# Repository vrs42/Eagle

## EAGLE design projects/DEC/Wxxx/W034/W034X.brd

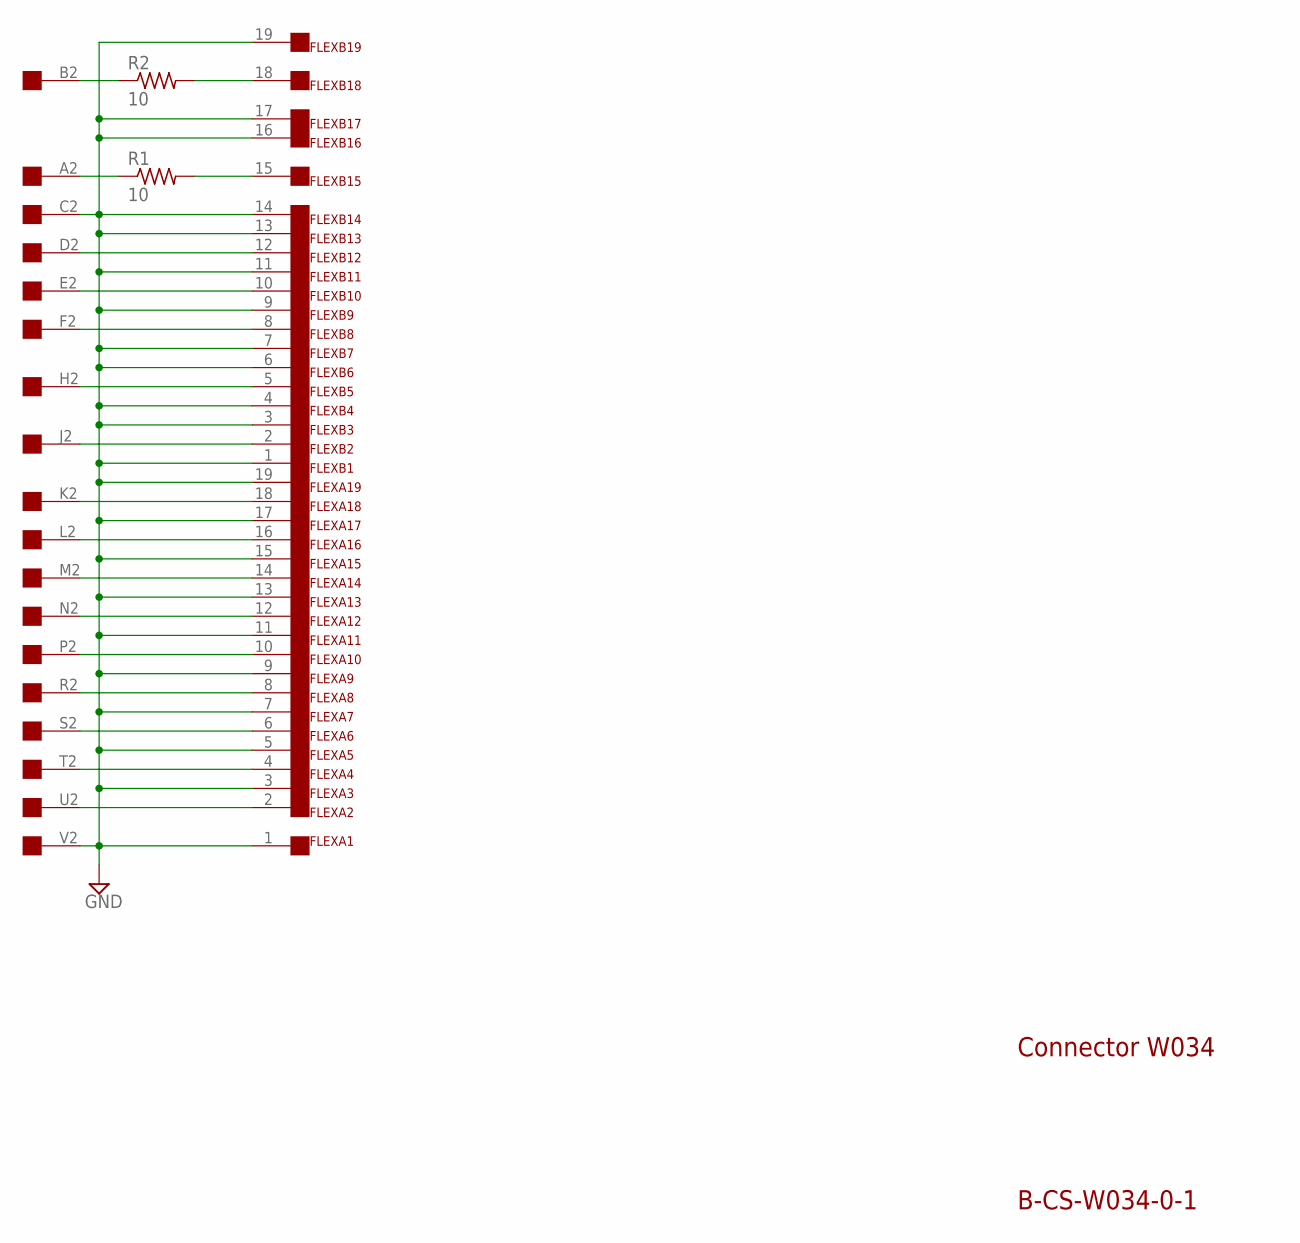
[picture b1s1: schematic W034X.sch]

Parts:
FLEXA: FLEX19
FLEXB: FLEX19
R1, R2: 10; 0207/10
U$2: EDGE-1; EDGE-CON1

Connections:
GND: FLEXA.1, FLEXA.3, FLEXA.5, FLEXA.7, FLEXA.9, FLEXA.11, FLEXA.13, FLEXA.15, FLEXA.17, FLEXA.19, FLEXB.1, FLEXB.3, FLEXB.4, FLEXB.6, FLEXB.7, FLEXB.9, FLEXB.11, FLEXB.13, FLEXB.14, FLEXB.16, FLEXB.17, FLEXB.19, U$2.C2, U$2.V2
unnamed: FLEXB.10, U$2.E2
unnamed: FLEXB.5, U$2.H2
unnamed: FLEXA.18, U$2.K2
unnamed: FLEXA.14, U$2.M2
unnamed: FLEXA.10, U$2.P2
unnamed: FLEXA.6, U$2.S2
unnamed: FLEXA.4, U$2.T2
unnamed: FLEXA.8, U$2.R2
unnamed: FLEXB.12, U$2.D2
unnamed: R2.1, U$2.B2
unnamed: R1.1, U$2.A2
unnamed: FLEXB.18, R2.2
unnamed: FLEXB.15, R1.2
unnamed: FLEXA.2, U$2.U2
unnamed: FLEXB.8, U$2.F2
unnamed: FLEXB.2, U$2.J2
unnamed: FLEXA.16, U$2.L2
unnamed: FLEXA.12, U$2.N2

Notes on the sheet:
Connector W034
B-CS-W034-0-1

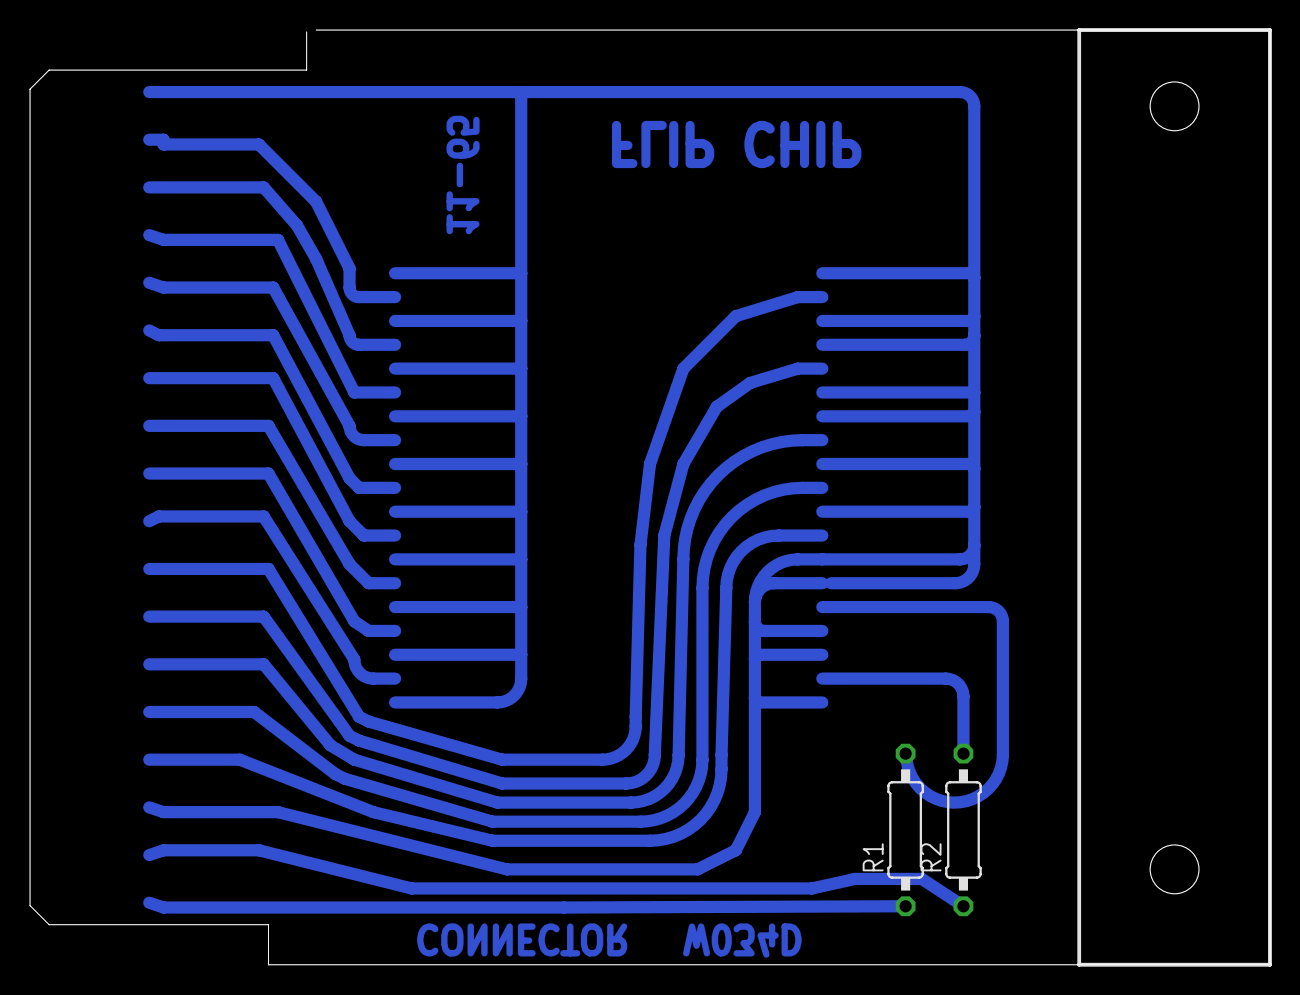
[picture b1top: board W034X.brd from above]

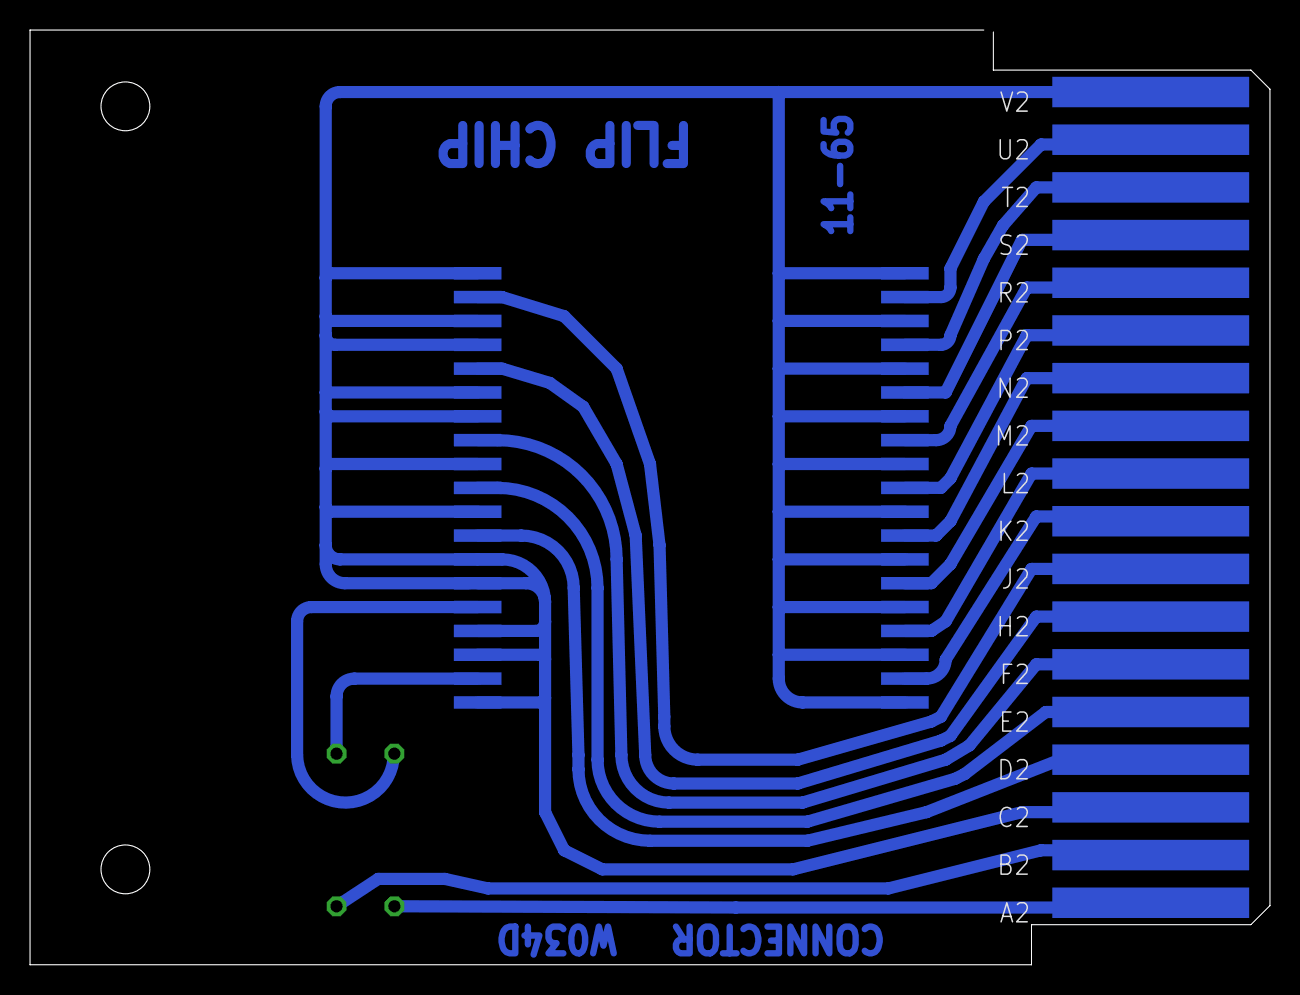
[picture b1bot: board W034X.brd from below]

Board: 2 copper layers, 82.5 x 62.2 mm, 5 parts (2 on the bottom side), 19 nets.

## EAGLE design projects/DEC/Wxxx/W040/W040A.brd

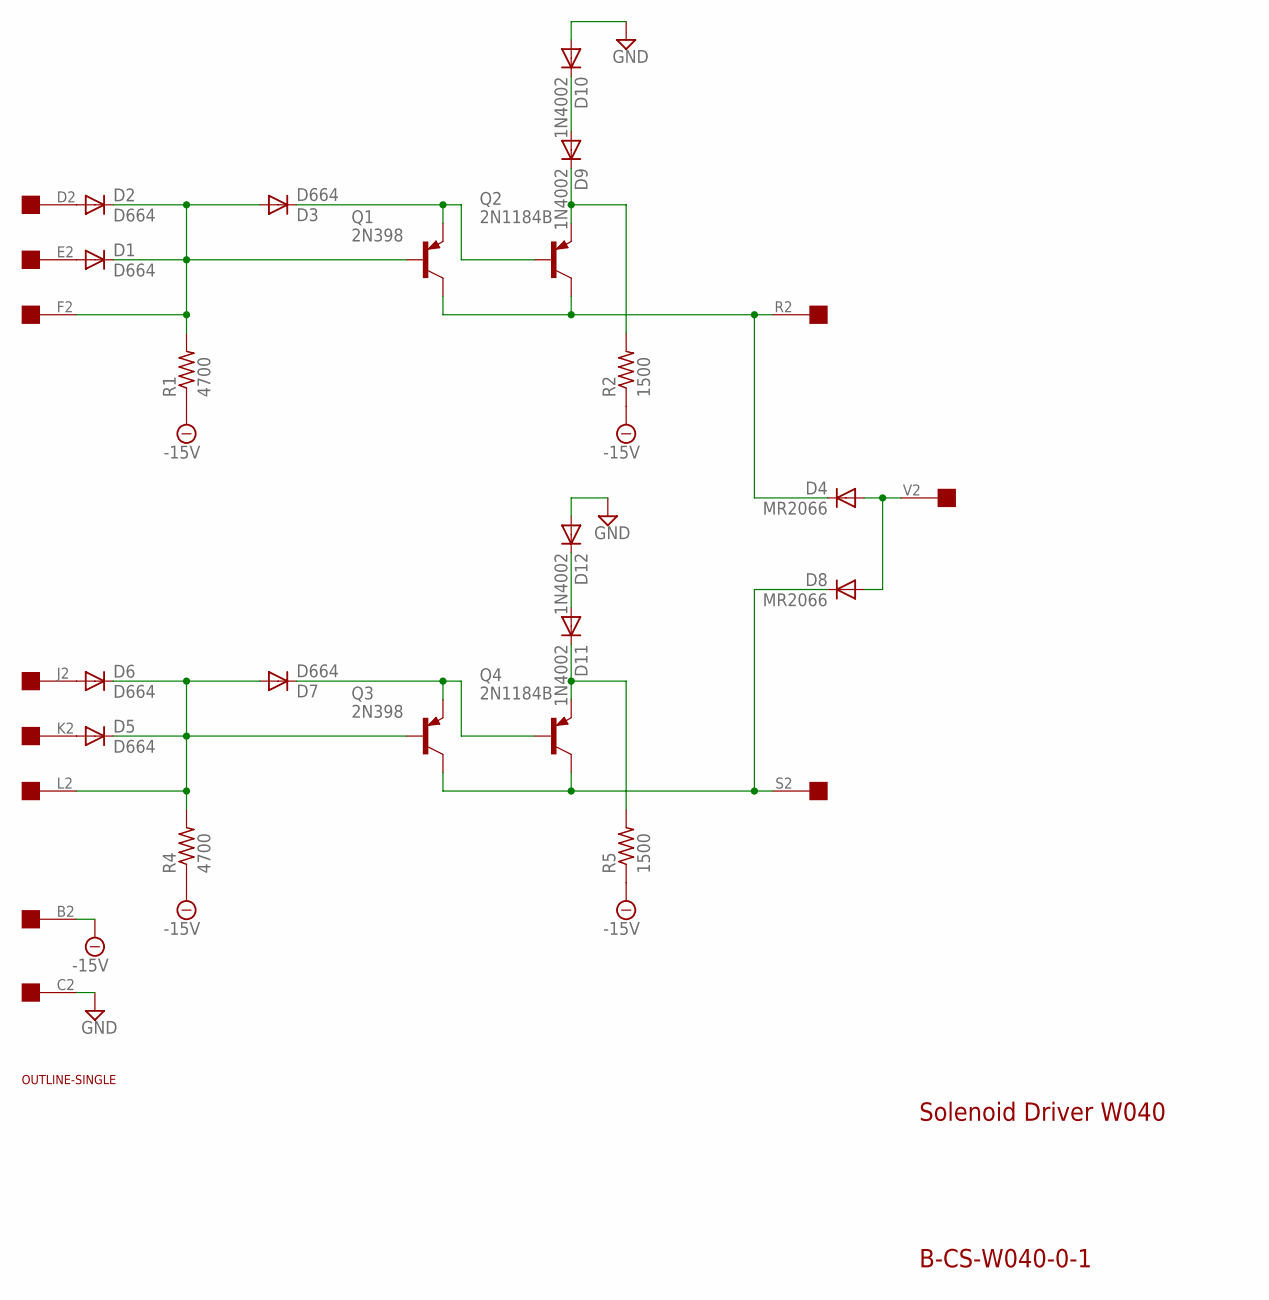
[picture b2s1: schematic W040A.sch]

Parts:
D1, D2, D3, D5, D6, D7: D664; DO35-10
D4, D8: MR2066; DO41-10
D9, D10, D11, D12: 1N4002; DO41-10
Q1, Q3: 2N398; TO39
Q2, Q4: 2N1184B; TO5
R1, R4: 4700; 0207/10
R2, R5: 1500; 0207/10
U$1: OUTLINE-SINGLE; SINGLE
U$2: EDGE-1; EDGE-CON1

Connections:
-15V: R1.1, R2.1, R4.1, R5.1, U$2.B2
GND: D10.A, D12.A, U$2.C2
unnamed: D1.A, U$2.E2
unnamed: D2.A, U$2.D2
unnamed: D1.C, D2.C, D3.A, Q1.2 (B), R1.2, U$2.F2
unnamed: D3.C, Q1.1 (E), Q2.2 (B)
unnamed: D9.A, D10.C
unnamed: D4.A, D8.A, U$2.V2
unnamed: D4.C, Q1.3 (C), Q2.3 (C), U$2.R2
unnamed: D5.A, U$2.K2
unnamed: D6.A, U$2.J2
unnamed: D5.C, D6.C, D7.A, Q3.2 (B), R4.2, U$2.L2
unnamed: D7.C, Q3.1 (E), Q4.2 (B)
unnamed: D9.C, Q2.1 (E), R2.2
unnamed: D8.C, Q3.3 (C), Q4.3 (C), U$2.S2
unnamed: D11.C, Q4.1 (E), R5.2
unnamed: D11.A, D12.C

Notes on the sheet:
Solenoid Driver W040
B-CS-W040-0-1

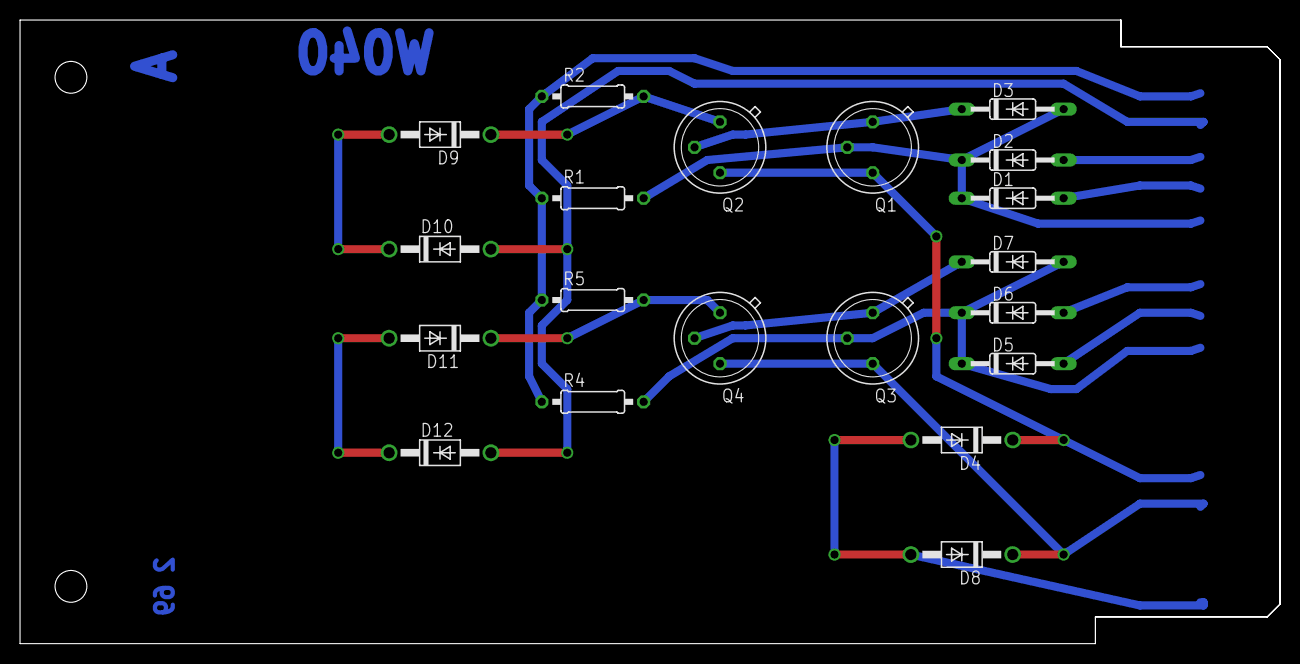
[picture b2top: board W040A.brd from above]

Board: 2 copper layers, 125.7 x 62.2 mm, 22 parts (0 on the bottom side), 17 nets.

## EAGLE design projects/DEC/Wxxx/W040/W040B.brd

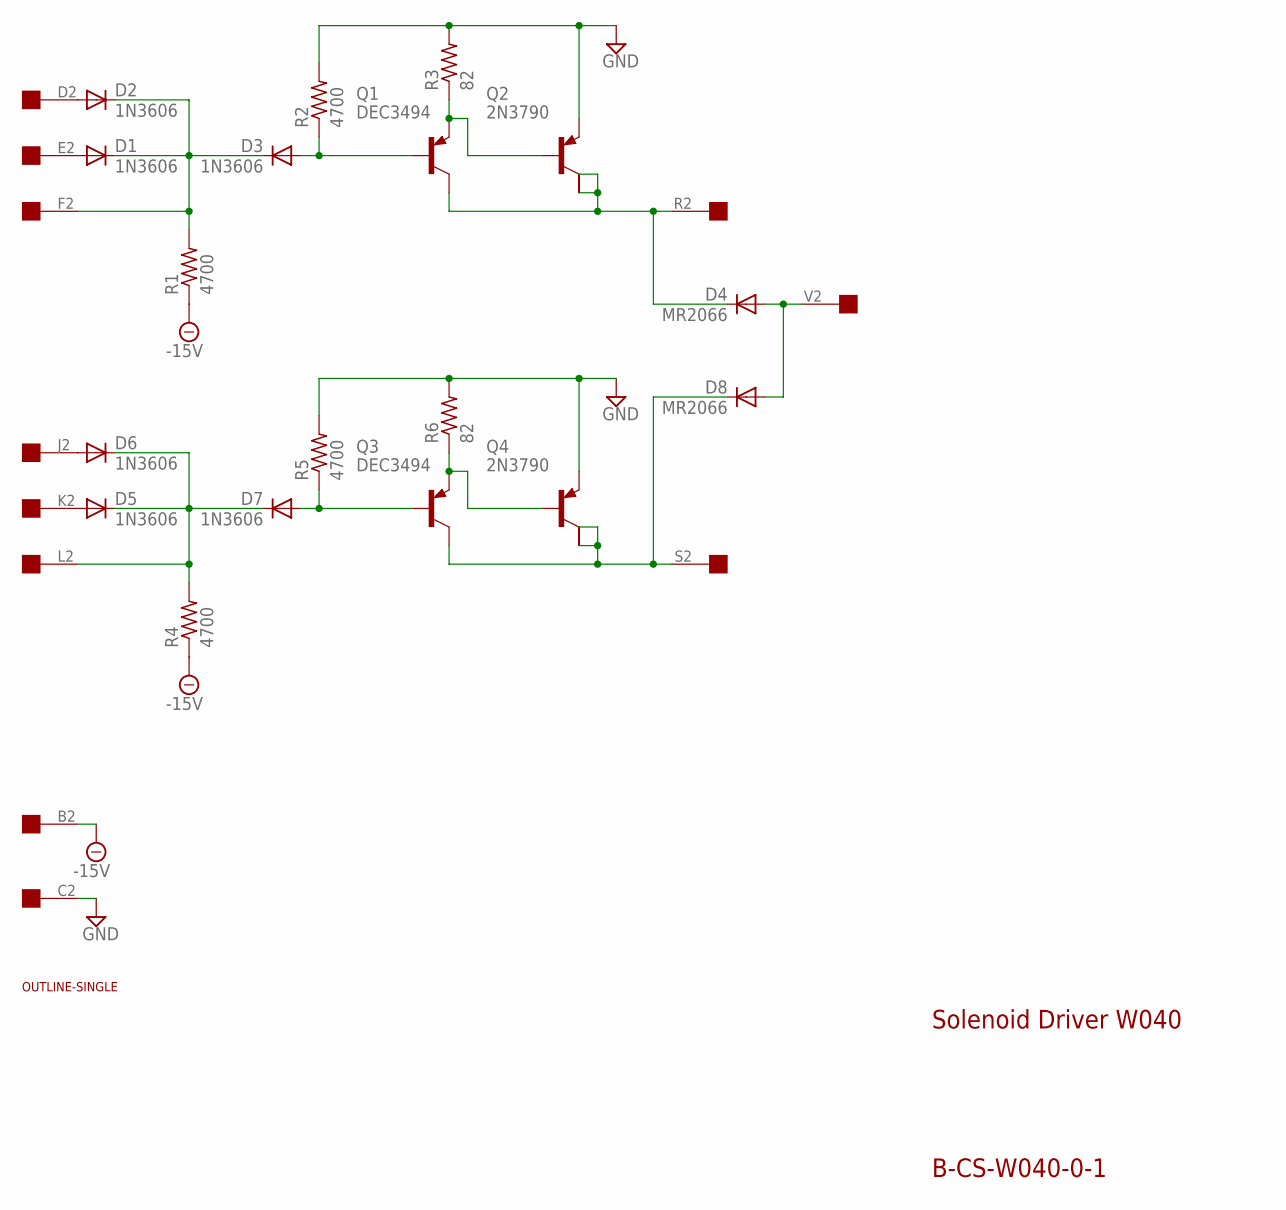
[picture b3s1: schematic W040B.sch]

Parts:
D1, D2, D3, D5, D6, D7: 1N3606; DO35-10
D4, D8: MR2066; DO41-10
Q1, Q3: DEC3494; TO39
Q2, Q4: 2N3790; TO3
R1, R2, R4, R5: 4700; 0207/10
R3, R6: 82; 0207/10
U$1: OUTLINE-SINGLE; SINGLE
U$2: EDGE-1; EDGE-CON1

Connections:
-15V: R1.1, R4.1, U$2.B2
GND: Q2.E, Q4.E, R2.2, R3.2, R5.2, R6.2, U$2.C2
unnamed: D1.A, U$2.E2
unnamed: D2.A, U$2.D2
unnamed: D1.C, D2.C, D3.C, R1.2, U$2.F2
unnamed: D3.A, Q1.2 (B), R2.1
unnamed: Q1.1 (E), Q2.B, R3.1
unnamed: D4.A, D8.A, U$2.V2
unnamed: D4.C, Q1.3 (C), Q2.C, Q2.C/, U$2.R2
unnamed: D5.A, U$2.K2
unnamed: D6.A, U$2.J2
unnamed: D5.C, D6.C, D7.C, R4.2, U$2.L2
unnamed: D7.A, Q3.2 (B), R5.1
unnamed: Q3.1 (E), Q4.B, R6.1
unnamed: D8.C, Q3.3 (C), Q4.C, Q4.C/, U$2.S2

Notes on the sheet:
Solenoid Driver W040
B-CS-W040-0-1

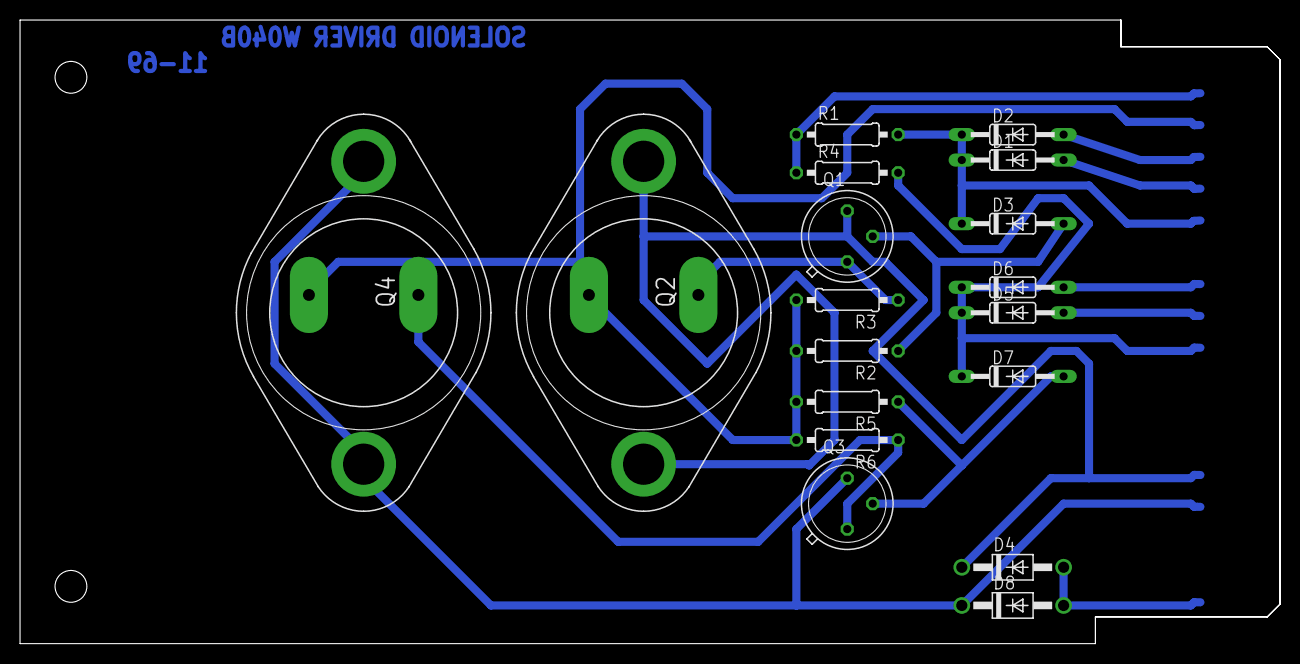
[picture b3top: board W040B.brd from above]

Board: 2 copper layers, 125.7 x 62.2 mm, 20 parts (0 on the bottom side), 15 nets.

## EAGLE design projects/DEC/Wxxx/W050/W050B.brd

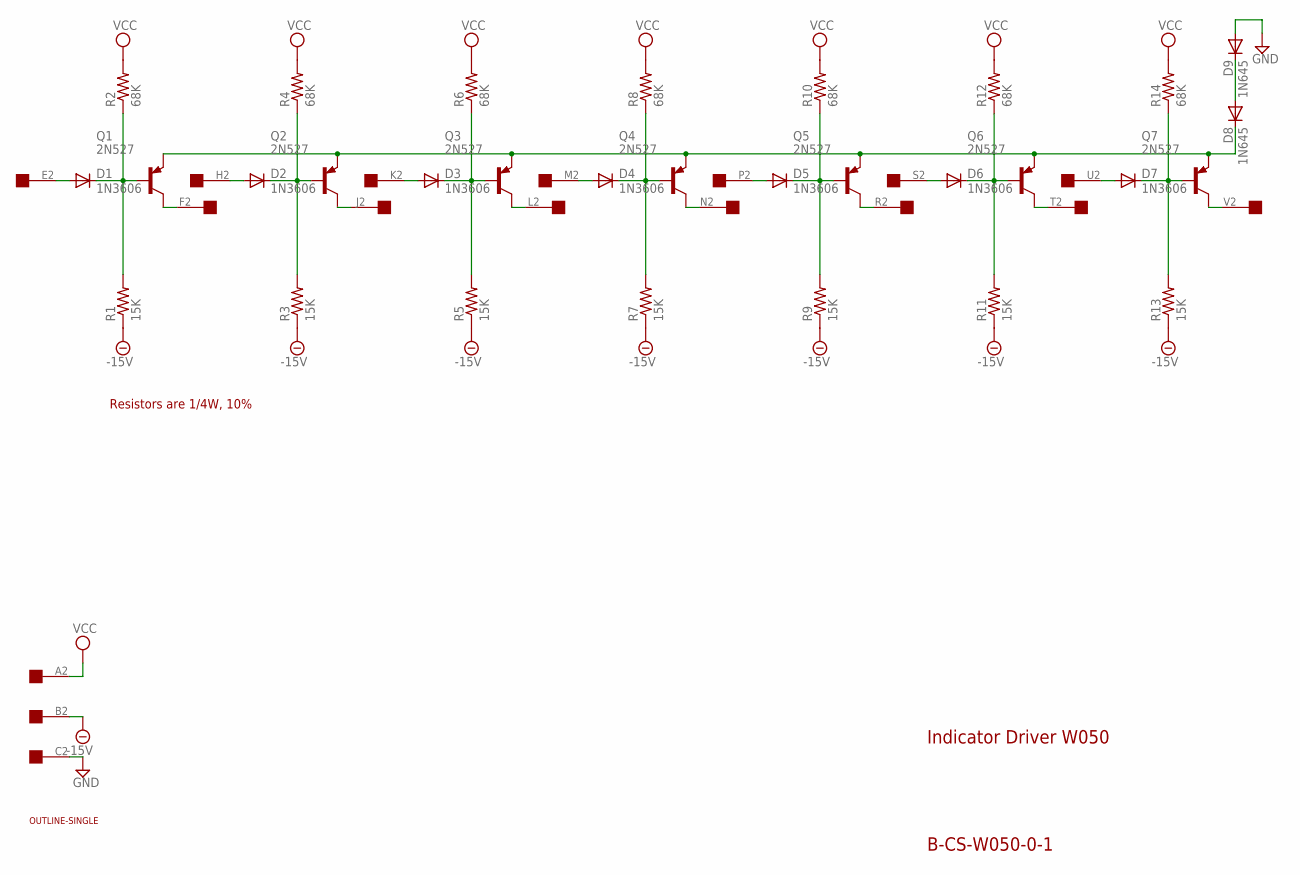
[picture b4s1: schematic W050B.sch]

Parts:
D1, D2, D3, D4, D5, D6, D7: 1N3606; DO35-10
D8, D9: 1N645; DO35-10
EDGE: EDGE-1; EDGE-CON1
Q1, Q2, Q3, Q4, Q5, Q6, Q7: 2N527; TO39
R1, R3, R5, R7, R9, R11, R13: 15K; 0207/10
R2, R4, R6, R8, R10, R12, R14: 68K; 0207/10
U$1: OUTLINE-SINGLE; SINGLE

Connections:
-15V: EDGE.B2, R1.1, R3.1, R5.1, R7.1, R9.1, R11.1, R13.1
GND: D9.A, EDGE.C2
unnamed: D1.C, Q1.2 (B), R1.2, R2.1
unnamed: EDGE.F2, Q1.3 (C)
unnamed: D1.A, EDGE.E2
unnamed: D2.C, Q2.2 (B), R3.2, R4.1
unnamed: EDGE.J2, Q2.3 (C)
unnamed: D6.A, EDGE.S2
unnamed: D4.C, Q4.2 (B), R7.2, R8.1
unnamed: EDGE.N2, Q4.3 (C)
unnamed: D7.A, EDGE.U2
unnamed: D3.C, Q3.2 (B), R5.2, R6.1
unnamed: EDGE.L2, Q3.3 (C)
unnamed: D5.A, EDGE.P2
unnamed: D5.C, Q5.2 (B), R9.2, R10.1
unnamed: EDGE.R2, Q5.3 (C)
unnamed: D4.A, EDGE.M2
unnamed: D6.C, Q6.2 (B), R11.2, R12.1
unnamed: EDGE.T2, Q6.3 (C)
unnamed: D3.A, EDGE.K2
unnamed: D7.C, Q7.2 (B), R13.2, R14.1
unnamed: EDGE.V2, Q7.3 (C)
unnamed: D2.A, EDGE.H2
unnamed: D8.C, Q1.1 (E), Q2.1 (E), Q3.1 (E), Q4.1 (E), Q5.1 (E), Q6.1 (E), Q7.1 (E)
unnamed: D8.A, D9.C
VCC: EDGE.A2, R2.2, R4.2, R6.2, R8.2, R10.2, R12.2, R14.2

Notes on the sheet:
Indicator Driver W050
Resistors are 1/4W, 10%
B-CS-W050-0-1

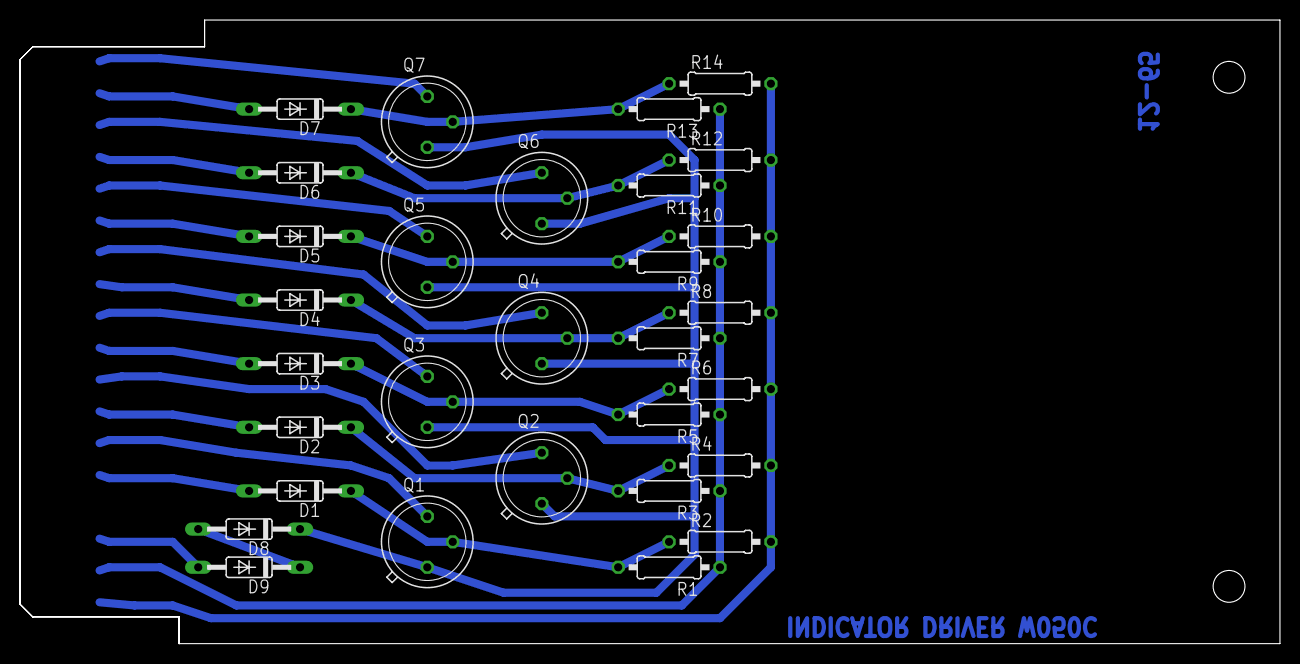
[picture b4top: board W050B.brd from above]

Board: 2 copper layers, 125.7 x 62.2 mm, 32 parts (0 on the bottom side), 26 nets.

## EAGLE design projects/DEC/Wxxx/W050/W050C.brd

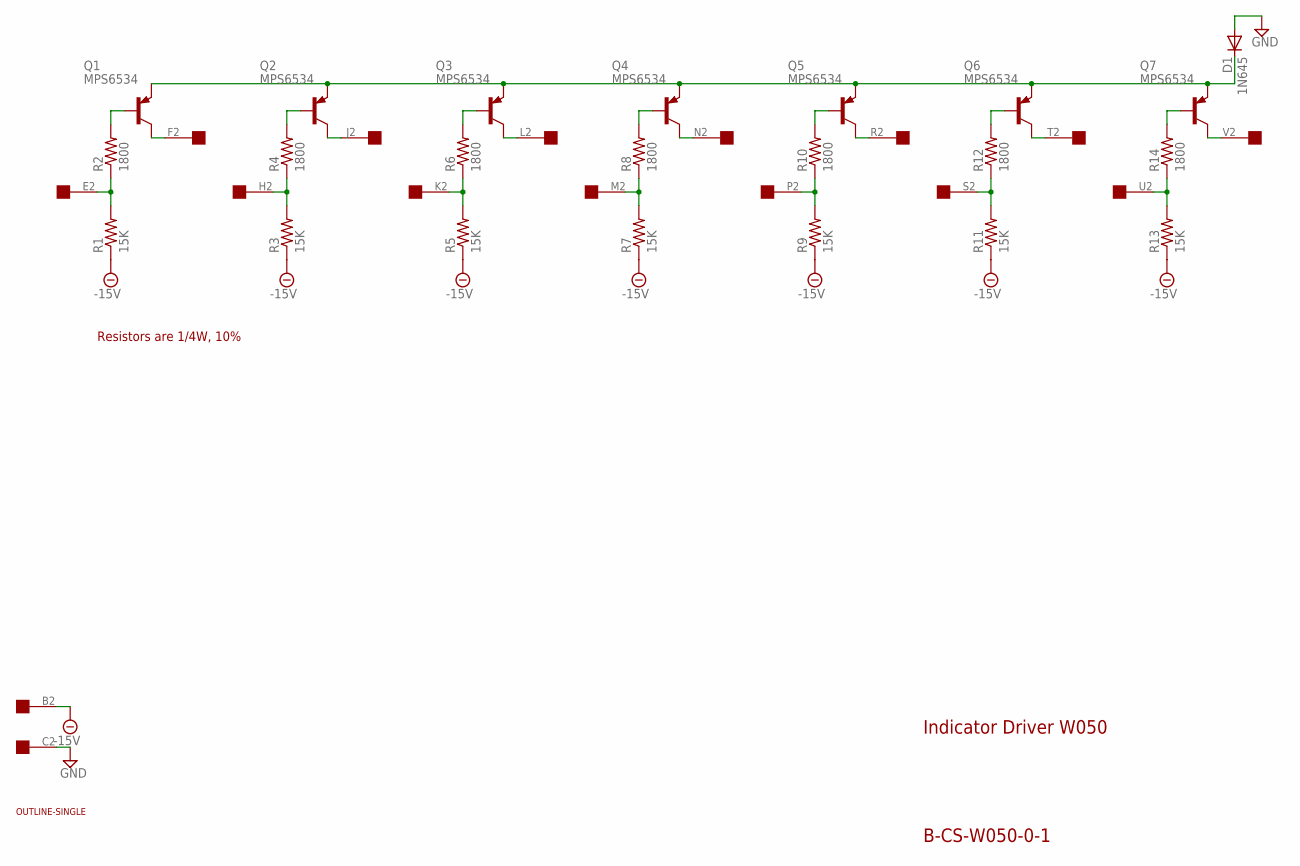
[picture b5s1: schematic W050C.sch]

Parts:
D1: 1N645; DO35-10
EDGE: EDGE-1; EDGE-CON1
Q1, Q2, Q3, Q4, Q5, Q6, Q7: MPS6534; TO39
R1, R3, R5, R7, R9, R11, R13: 15K; 0207/10
R2, R4, R6, R8, R10, R12, R14: 1800; 0207/10
U$1: OUTLINE-SINGLE; SINGLE

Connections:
-15V: EDGE.B2, R1.1, R3.1, R5.1, R7.1, R9.1, R11.1, R13.1
GND: D1.A, EDGE.C2
unnamed: EDGE.E2, R1.2, R2.1
unnamed: EDGE.F2, Q1.3 (C)
unnamed: Q1.2 (B), R2.2
unnamed: EDGE.H2, R3.2, R4.1
unnamed: EDGE.J2, Q2.3 (C)
unnamed: Q2.2 (B), R4.2
unnamed: EDGE.M2, R7.2, R8.1
unnamed: EDGE.N2, Q4.3 (C)
unnamed: Q4.2 (B), R8.2
unnamed: EDGE.K2, R5.2, R6.1
unnamed: EDGE.L2, Q3.3 (C)
unnamed: Q3.2 (B), R6.2
unnamed: EDGE.P2, R9.2, R10.1
unnamed: EDGE.R2, Q5.3 (C)
unnamed: Q5.2 (B), R10.2
unnamed: EDGE.S2, R11.2, R12.1
unnamed: EDGE.T2, Q6.3 (C)
unnamed: Q6.2 (B), R12.2
unnamed: EDGE.U2, R13.2, R14.1
unnamed: EDGE.V2, Q7.3 (C)
unnamed: Q7.2 (B), R14.2
unnamed: D1.C, Q1.1 (E), Q2.1 (E), Q3.1 (E), Q4.1 (E), Q5.1 (E), Q6.1 (E), Q7.1 (E)

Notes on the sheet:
Indicator Driver W050
Resistors are 1/4W, 10%
B-CS-W050-0-1

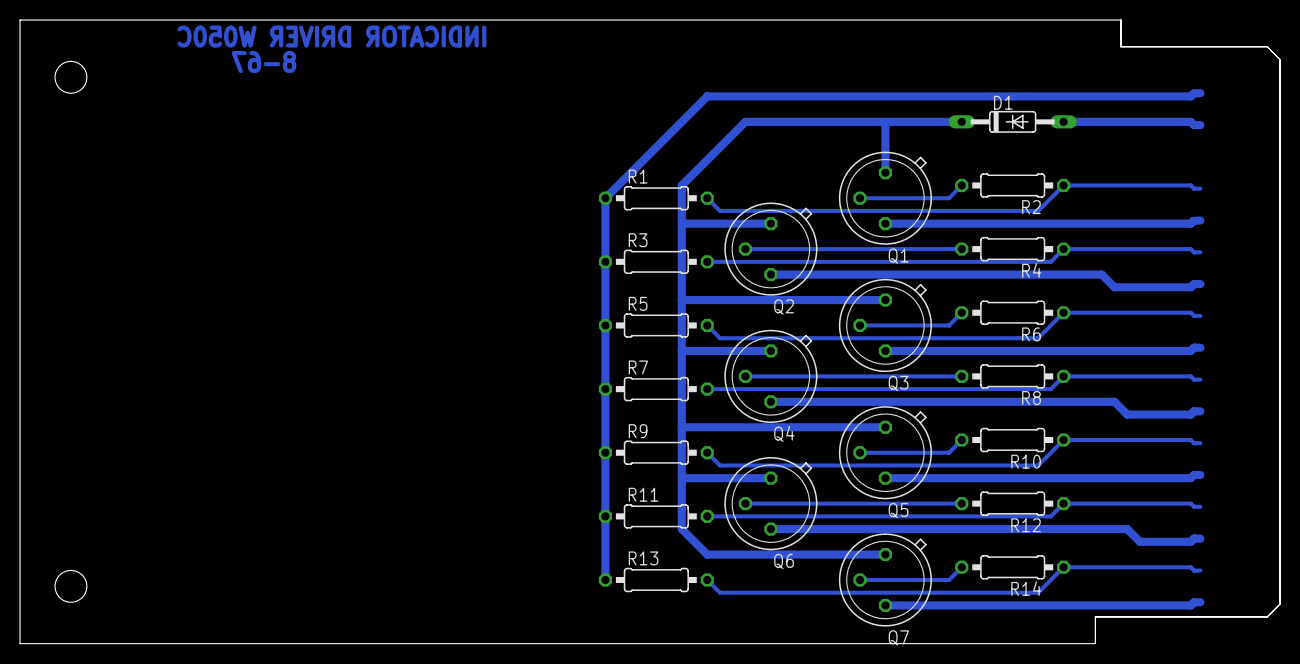
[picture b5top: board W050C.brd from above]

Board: 2 copper layers, 125.7 x 62.2 mm, 24 parts (0 on the bottom side), 24 nets.

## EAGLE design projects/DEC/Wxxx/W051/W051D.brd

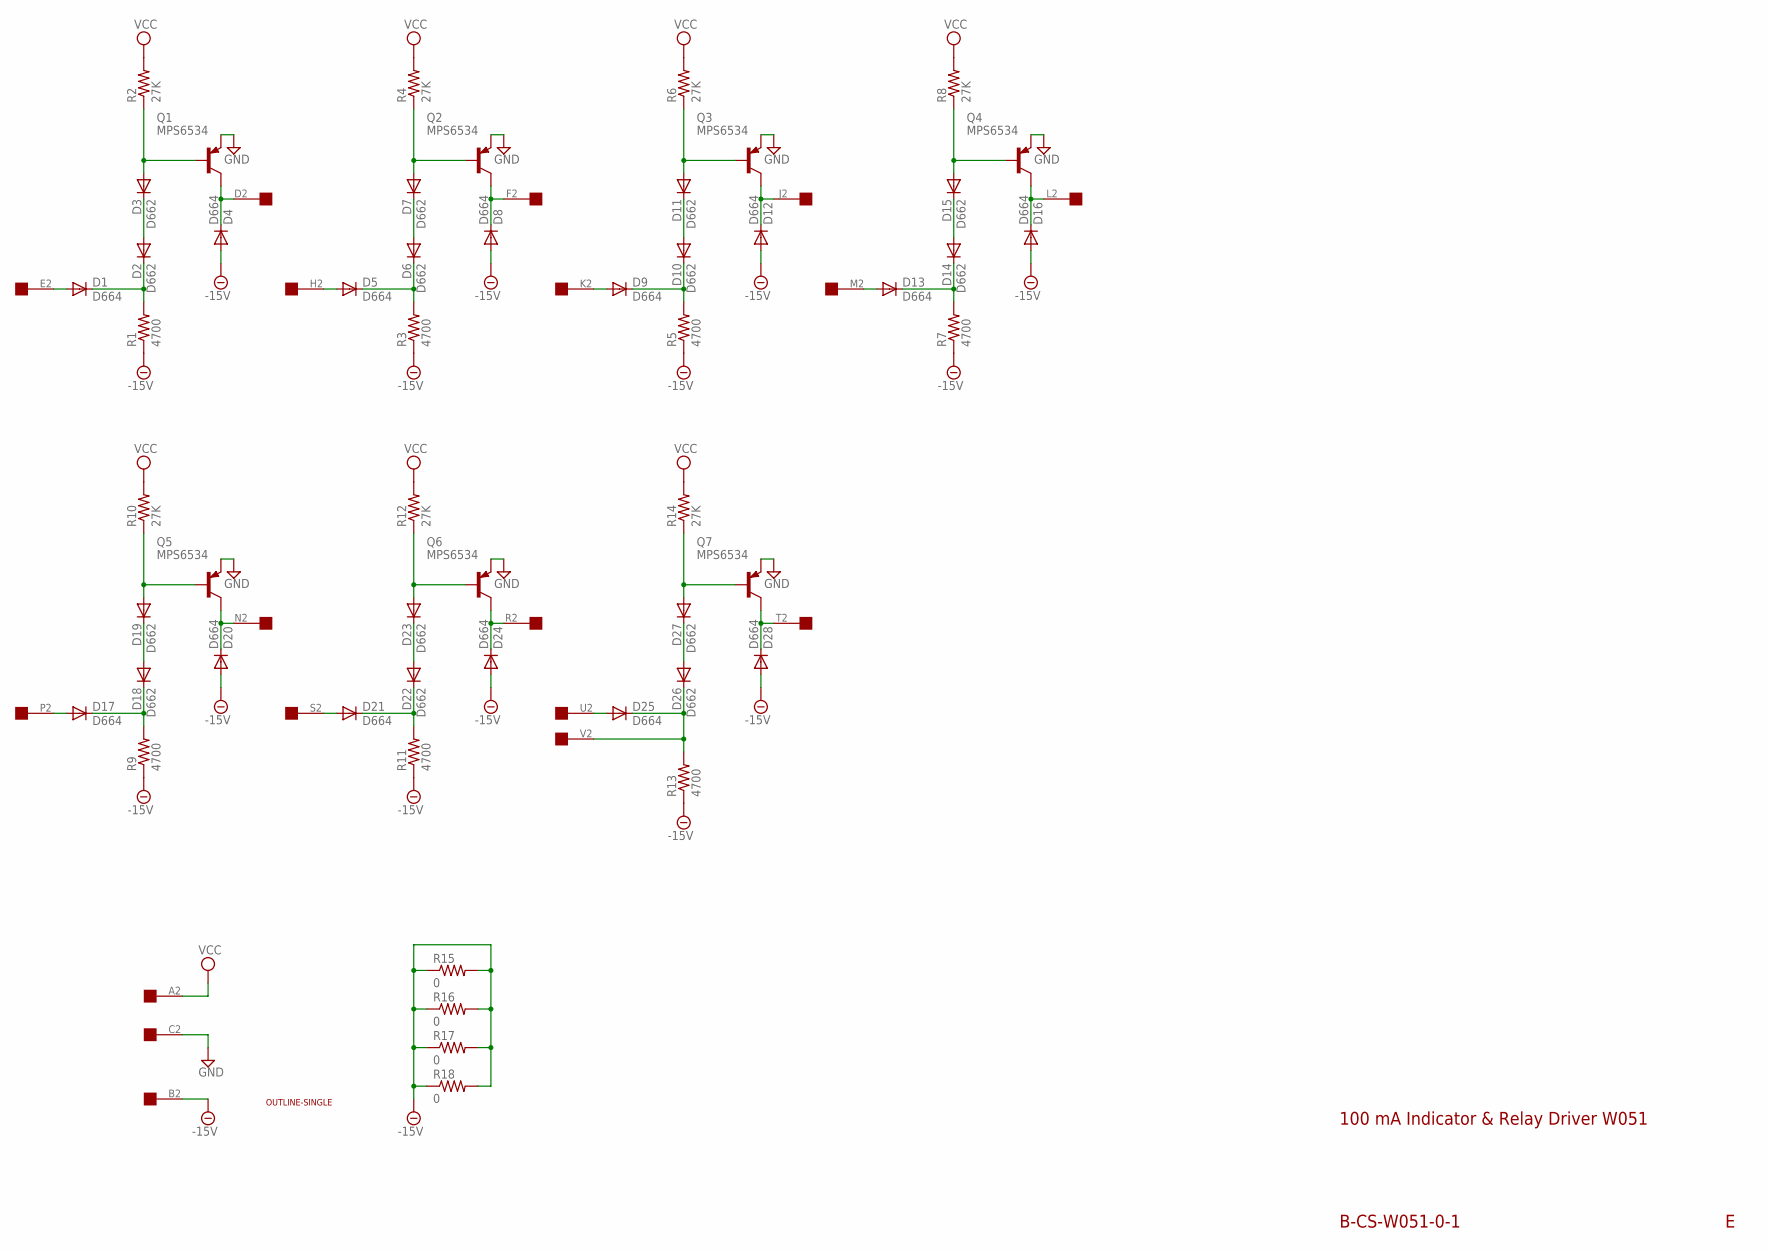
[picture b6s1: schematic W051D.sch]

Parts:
D1, D4, D5, D8, D9, D12, D13, D16, D17, D20, D21, D24, D25, D28: D664; DO35-10
D2, D3, D6, D7, D10, D11, D14, D15, D18, D19, D22, D23, D26, D27: D662; DO35-10
Q1, Q2, Q3, Q4, Q5, Q6, Q7: MPS6534; TO5
R1, R3, R5, R7, R9, R11, R13: 4700; 0207/10
R2, R4, R6, R8, R10, R12, R14: 27K; 0207/10
R15, R16, R17, R18: 0; 0207/10
U$1: OUTLINE-SINGLE; SINGLE
U$2: EDGE-1; EDGE-CON1

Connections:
-15V: D4.A, D8.A, D12.A, D16.A, D20.A, D24.A, D28.A, R1.1, R3.1, R5.1, R7.1, R9.1, R11.1, R13.1, R15.1, R15.2, R16.1, R16.2, R17.1, R17.2, R18.1, R18.2, U$2.B2
GND: Q1.1 (E), Q2.1 (E), Q3.1 (E), Q4.1 (E), Q5.1 (E), Q6.1 (E), Q7.1 (E), U$2.C2
unnamed: D1.C, D2.C, R1.2
unnamed: D2.A, D3.C
unnamed: D3.A, Q1.2 (B), R2.1
unnamed: D4.C, Q1.3 (C), U$2.D2
unnamed: D1.A, U$2.E2
unnamed: D5.C, D6.C, R3.2
unnamed: D6.A, D7.C
unnamed: D7.A, Q2.2 (B), R4.1
unnamed: D8.C, Q2.3 (C), U$2.F2
unnamed: D5.A, U$2.H2
unnamed: D9.C, D10.C, R5.2
unnamed: D10.A, D11.C
unnamed: D11.A, Q3.2 (B), R6.1
unnamed: D12.C, Q3.3 (C), U$2.J2
unnamed: D9.A, U$2.K2
unnamed: D13.C, D14.C, R7.2
unnamed: D14.A, D15.C
unnamed: D15.A, Q4.2 (B), R8.1
unnamed: D16.C, Q4.3 (C), U$2.L2
unnamed: D13.A, U$2.M2
unnamed: D17.C, D18.C, R9.2
unnamed: D18.A, D19.C
unnamed: D19.A, Q5.2 (B), R10.1
unnamed: D28.C, Q7.3 (C), U$2.T2
unnamed: D17.A, U$2.P2
unnamed: D21.C, D22.C, R11.2
unnamed: D22.A, D23.C
unnamed: D23.A, Q6.2 (B), R12.1
unnamed: D24.C, Q6.3 (C), U$2.R2
unnamed: D21.A, U$2.S2
unnamed: D25.C, D26.C, R13.2, U$2.V2
unnamed: D26.A, D27.C
unnamed: D27.A, Q7.2 (B), R14.1
unnamed: D20.C, Q5.3 (C), U$2.N2
unnamed: D25.A, U$2.U2
VCC: R2.2, R4.2, R6.2, R8.2, R10.2, R12.2, R14.2, U$2.A2

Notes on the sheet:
B-CS-W051-0-1
100 mA Indicator & Relay Driver W051

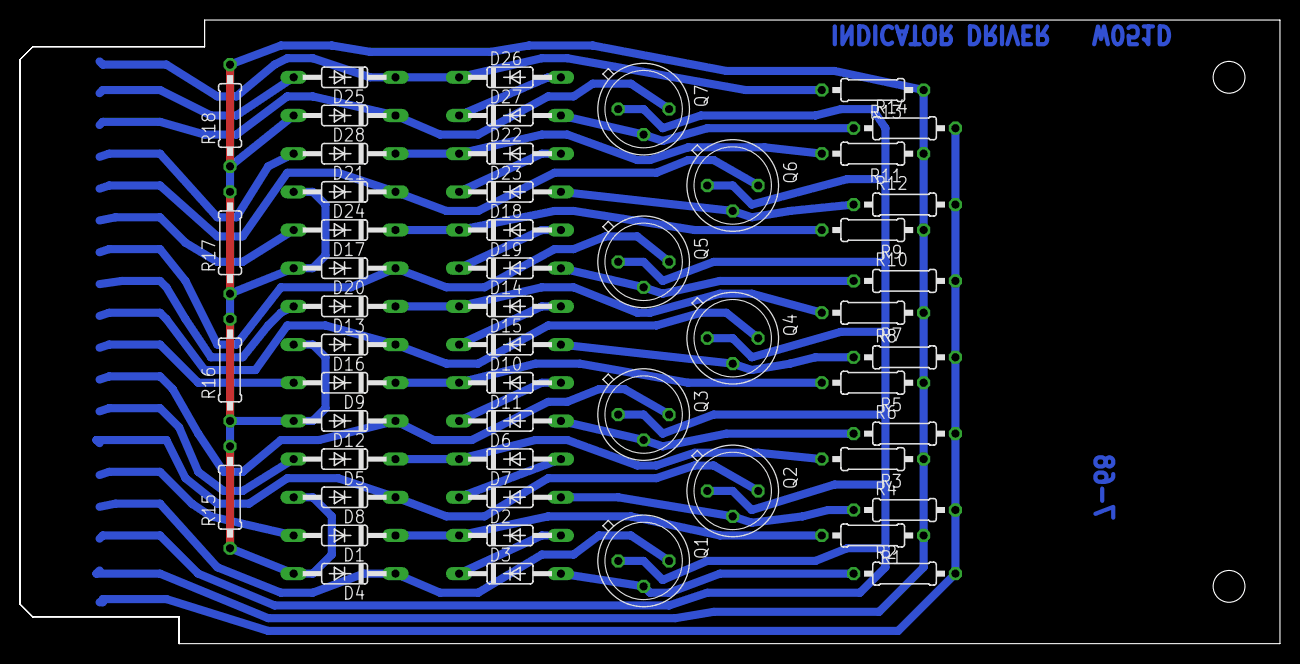
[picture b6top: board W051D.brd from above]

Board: 2 copper layers, 125.7 x 62.2 mm, 55 parts (0 on the bottom side), 38 nets.
